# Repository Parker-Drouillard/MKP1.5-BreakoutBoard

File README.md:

# MKP1.5-BreakoutBoard
A breakout board for supporting dual extrusion &amp; 6 pwm fan control for the Rambo 1.4 

This board supports a Teensy 2.0 slave device to the Rambo 1.4 over Serial. The purpose of this board is to expand the available IO of the Rambo 1.4 to be capable of supporting a dual extrusion system, as well as additional PWM fan controls.

## About this board
This board offers 6 5v fan headers for PWM switching via a darlington array. At this current time, it does not seem the max PWM speed of the Teensy 2.0 is sufficient to run the fans at less than 100% power, so for the time being it is simply a toggle of Off or On.
The board includes a 24V to 5V buck converter, capable of supporting 3A of power, of which only 2A is anticipated to be used. Additionally, 2 ports for PT1000 passthrough, and 2 ports for E3D PT100 Amplifier boards are provided. 
An onboard L298N allows for low voltage switching of 2 independant 24V systems, one of which is being used for the second extruder solenoid, and one will be used in the future fora dynamic extruder pressure motor. Both systems have 2 encontrol pins, 1 for forward, and 1 for reverse.

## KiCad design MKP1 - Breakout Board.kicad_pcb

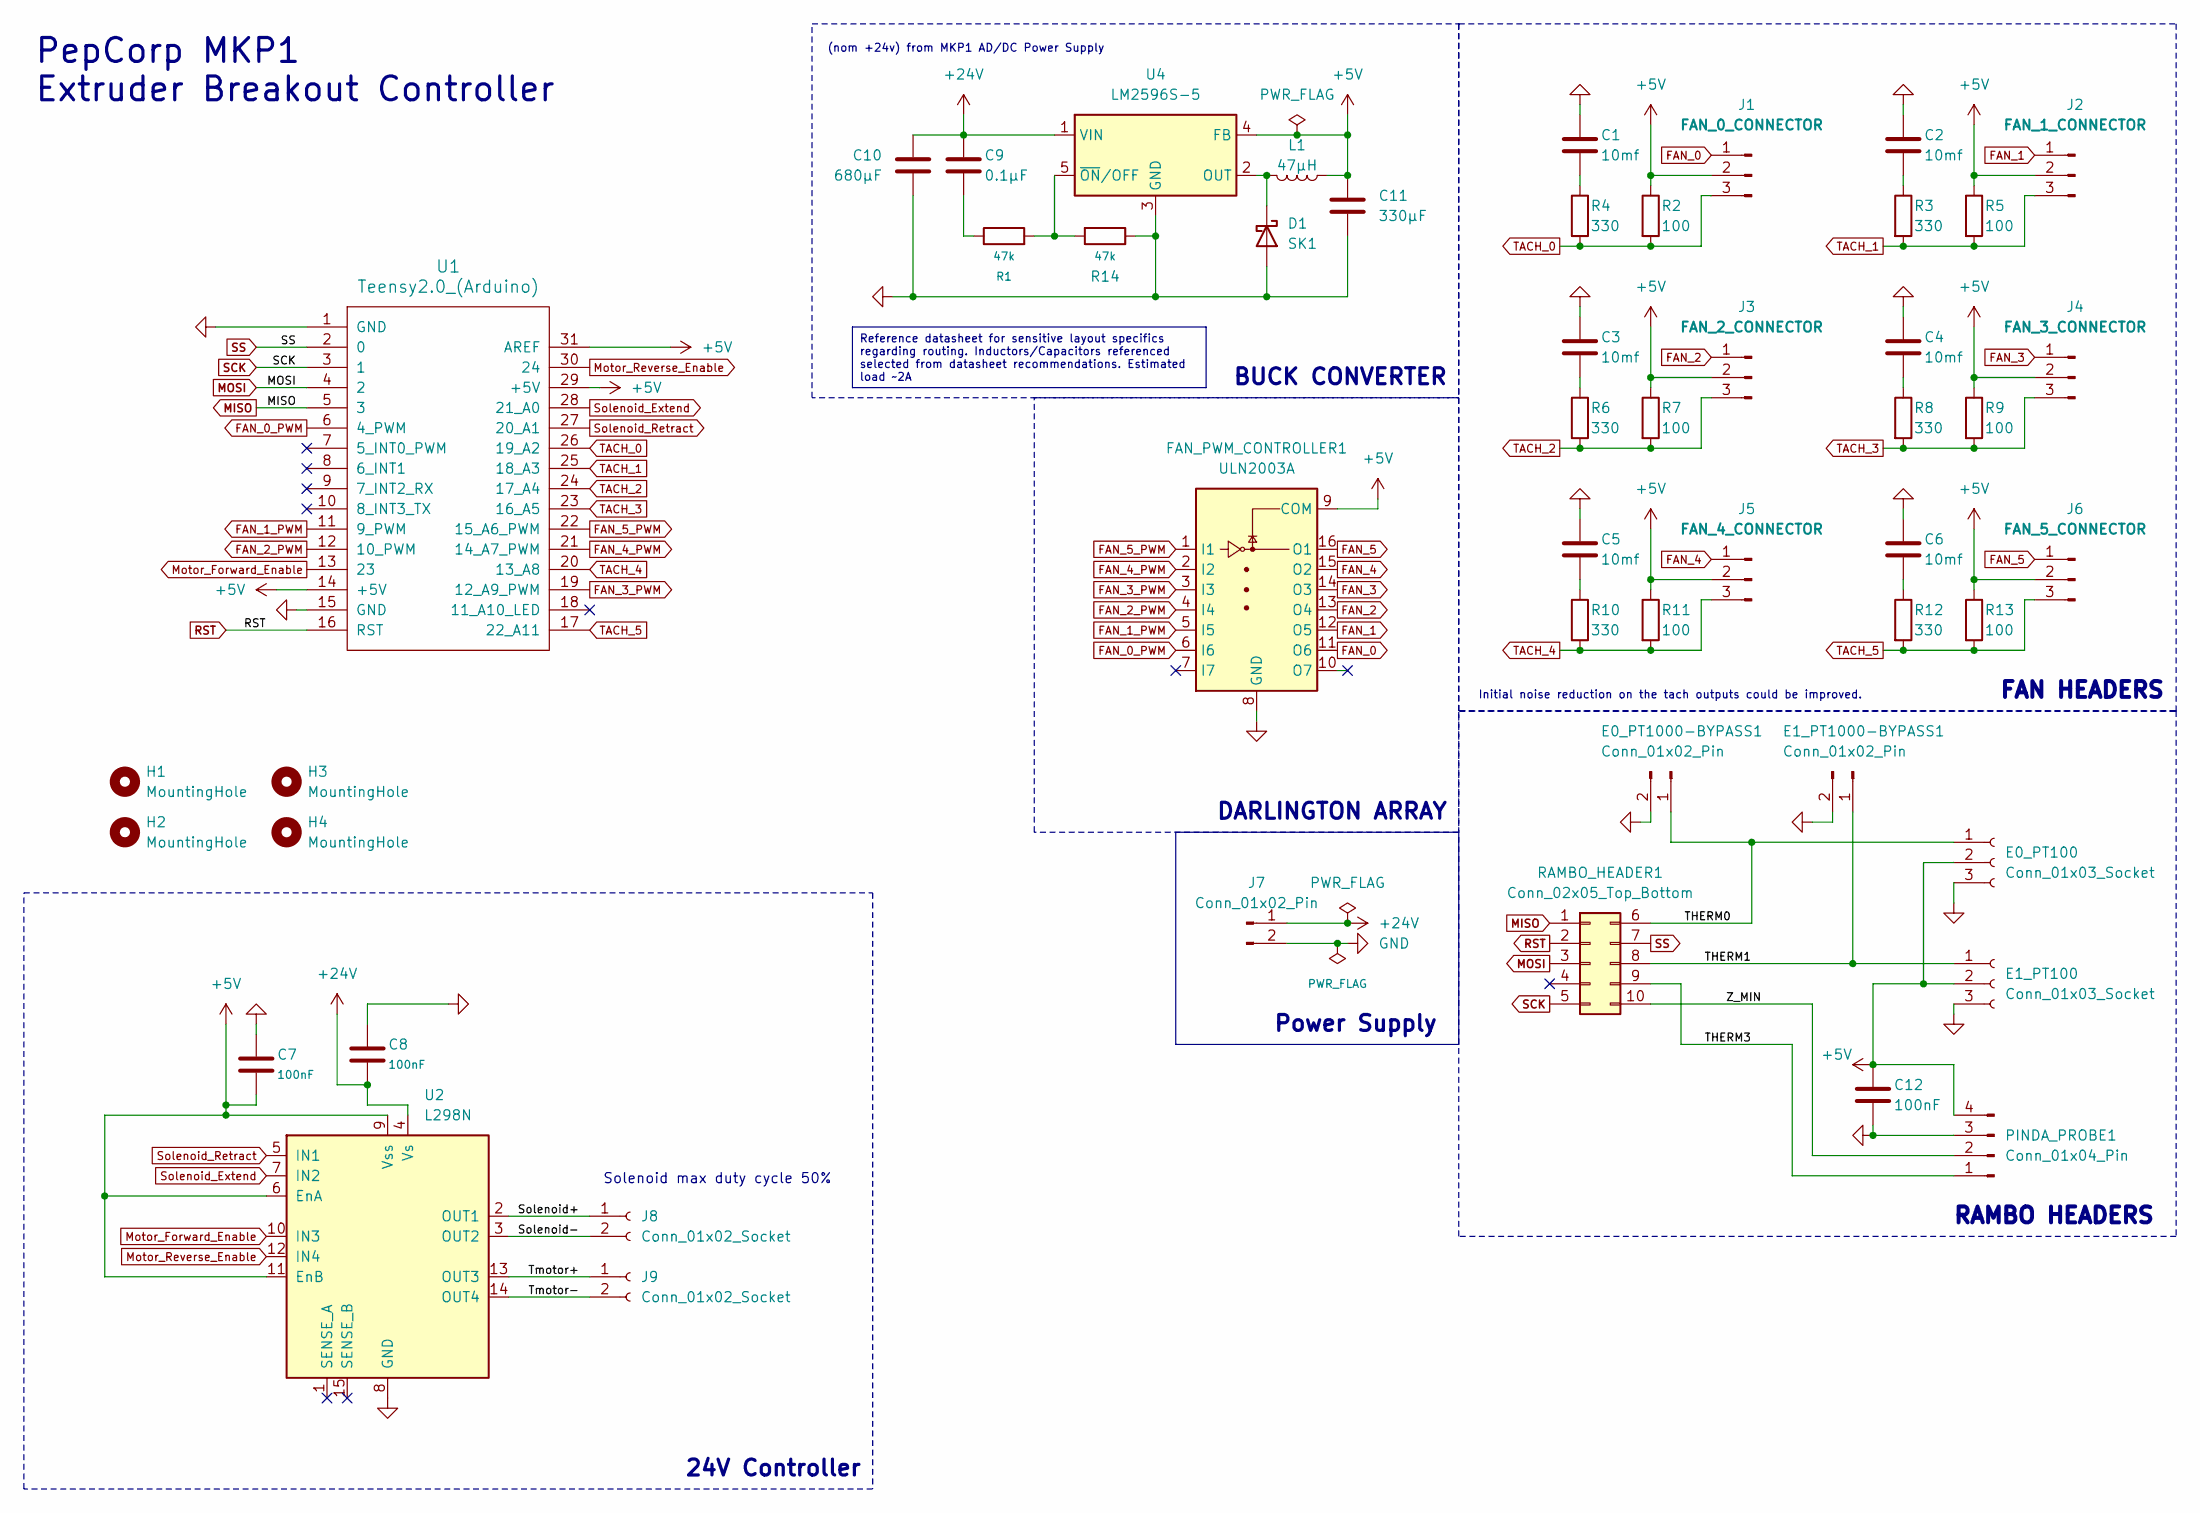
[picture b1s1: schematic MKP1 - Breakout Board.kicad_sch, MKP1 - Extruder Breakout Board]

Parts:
C1, C2, C3, C4, C5, C6: 10mf; C_0603_1608Metric_Pad1.08x0.95mm_HandSolder
C7, C8, C12: 100nF; C_0402_1005Metric_Pad0.74x0.62mm_HandSolder
C9: 0.1µF; C_0402_1005Metric_Pad0.74x0.62mm_HandSolder
C10: 680µF; C_0603_1608Metric_Pad1.08x0.95mm_HandSolder
C11: 330µF; C_0603_1608Metric_Pad1.08x0.95mm_HandSolder
D1: SK1; D_0603_1608Metric_Pad1.05x0.95mm_HandSolder
E0_PT100, E1_PT100: Conn_01x03_Socket; PinSocket_1x03_P2.00mm_Vertical
E0_PT1000-BYPASS1, E1_PT1000-BYPASS1: Conn_01x02_Pin; Molex_KK-254_AE-6410-02A_1x02_P2.54mm_Vertical
FAN_PWM_CONTROLLER1: ULN2003A; DIP-16_W7.62mm_Socket
H1, H2, H3, H4: MountingHole; MountingHole_3.2mm_M3
J1: FAN_0_CONNECTOR; Molex_KK-396_5273-03A_1x03_P3.96mm_Vertical
J2: FAN_1_CONNECTOR; Molex_KK-396_5273-03A_1x03_P3.96mm_Vertical
J3: FAN_2_CONNECTOR; Molex_KK-396_5273-03A_1x03_P3.96mm_Vertical
J4: FAN_3_CONNECTOR; Molex_KK-396_5273-03A_1x03_P3.96mm_Vertical
J5: FAN_4_CONNECTOR; Molex_KK-396_5273-03A_1x03_P3.96mm_Vertical
J6: FAN_5_CONNECTOR; Molex_KK-396_5273-03A_1x03_P3.96mm_Vertical
J7: Conn_01x02_Pin; Molex_KK-396_A-41791-0002_1x02_P3.96mm_Vertical
J8, J9: Conn_01x02_Socket; Molex_KK-254_AE-6410-02A_1x02_P2.54mm_Vertical
L1: 47µH; L_0402_1005Metric
PINDA_PROBE1: Conn_01x04_Pin; Molex_KK-396_5273-04A_1x04_P3.96mm_Vertical
R1, R14: 47k; R_0402_1005Metric
R2, R5, R7, R9, R11, R13: 100; R_0402_1005Metric
R3, R4, R6, R8, R10, R12: 330; R_0402_1005Metric
RAMBO_HEADER1: Conn_02x05_Top_Bottom; PinHeader_2x05_P2.00mm_Vertical
U1: Teensy2.0_(Arduino); Teensy2.0
U2: L298N; TO-220-15_P2.54x2.54mm_StaggerOdd_Lead4.58mm_Vertical
U4: LM2596S-5; TO-263-5_TabPin3

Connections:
+5V: C7.2, C11.1, C12.1, E0_PT100.2, E1_PT100.2, FAN_PWM_CONTROLLER1.9 (COM), J1.2, J2.2, J3.2, J4.2, J5.2, J6.2, L1.2, PINDA_PROBE1.4, R2.1, R5.1, R7.1, R9.1, R11.1, R13.1, U1.14 (+5V), U1.29 (+5V), U1.31 (AREF), U2.6 (EnA), U2.9 (Vss), U2.11 (EnB), U4.4 (FB); also elsewhere on the board
+24V: C8.2, C9.1, C10.2, J7.1, U2.4 (Vs), U4.1 (VIN)
/Solenoid+: J8.1, U2.2 (OUT1)
/Solenoid-: J8.2, U2.3 (OUT2)
/THERM0: E0_PT100.1, E0_PT1000-BYPASS1.1, RAMBO_HEADER1.6; also elsewhere on the board
/THERM1: E1_PT100.1, E1_PT1000-BYPASS1.1, RAMBO_HEADER1.8; also elsewhere on the board
/THERM3: PINDA_PROBE1.1, RAMBO_HEADER1.9; also elsewhere on the board
/Tmotor+: J9.1, U2.13 (OUT3)
/Tmotor-: J9.2, U2.14 (OUT4)
/Z_MIN: PINDA_PROBE1.2, RAMBO_HEADER1.10; also elsewhere on the board
FAN_0: FAN_PWM_CONTROLLER1.11 (O6), J1.1
FAN_0_PWM: FAN_PWM_CONTROLLER1.6 (I6), U1.6 (4_PWM)
FAN_1: FAN_PWM_CONTROLLER1.12 (O5), J2.1
FAN_1_PWM: FAN_PWM_CONTROLLER1.5 (I5), U1.11 (9_PWM)
FAN_2: FAN_PWM_CONTROLLER1.13 (O4), J3.1
FAN_2_PWM: FAN_PWM_CONTROLLER1.4 (I4), U1.12 (10_PWM)
FAN_3: FAN_PWM_CONTROLLER1.14 (O3), J4.1
FAN_3_PWM: FAN_PWM_CONTROLLER1.3 (I3), U1.19 (12_A9_PWM)
FAN_4: FAN_PWM_CONTROLLER1.15 (O2), J5.1
FAN_4_PWM: FAN_PWM_CONTROLLER1.2 (I2), U1.21 (14_A7_PWM)
FAN_5: FAN_PWM_CONTROLLER1.16 (O1), J6.1
FAN_5_PWM: FAN_PWM_CONTROLLER1.1 (I1), U1.22 (15_A6_PWM)
GND: C1.1, C2.1, C3.1, C4.1, C5.1, C6.1, C7.1, C8.1, C10.1, C11.2, C12.2, D1.2 (A), E0_PT100.3, E0_PT1000-BYPASS1.2, E1_PT100.3, E1_PT1000-BYPASS1.2, FAN_PWM_CONTROLLER1.8 (GND), J7.2, PINDA_PROBE1.3, R14.1, U1.1 (GND), U1.15 (GND), U2.8 (GND), U4.3 (GND); also elsewhere on the board
MISO: RAMBO_HEADER1.1, U1.5 (3)
MOSI: RAMBO_HEADER1.3, U1.4 (2)
Motor_Forward_Enable: U1.13 (23), U2.10 (IN3)
Motor_Reverse_Enable: U1.30 (24), U2.12 (IN4)
unnamed: C1.2, R4.1
unnamed: C2.2, R3.1
unnamed: C3.2, R6.1
unnamed: C4.2, R8.1
unnamed: C5.2, R10.1
unnamed: C6.2, R12.1
unnamed: C9.2, R1.1
unnamed: D1.1 (K), L1.1, U4.2 (OUT)
unnamed: R1.2, R14.2, U4.5 (~ON/OFF)
RST: RAMBO_HEADER1.2, U1.16 (RST)
SCK: RAMBO_HEADER1.5, U1.3 (1)
SS: RAMBO_HEADER1.7, U1.2 (0)
Solenoid_Extend: U1.28 (21_A0), U2.7 (IN2)
Solenoid_Retract: U1.27 (20_A1), U2.5 (IN1)
TACH_0: J1.3, R2.2, R4.2, U1.26 (19_A2)
TACH_1: J2.3, R3.2, R5.2, U1.25 (18_A3)
TACH_2: J3.3, R6.2, R7.2, U1.24 (17_A4)
TACH_3: J4.3, R8.2, R9.2, U1.23 (16_A5)
TACH_4: J5.3, R10.2, R11.2, U1.20 (13_A8)
TACH_5: J6.3, R12.2, R13.2, U1.17 (22_A11)

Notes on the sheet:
Reference datasheet for sensitive layout specifics regarding routing. Inductors/Capacitors referenced selected from datasheet recommendations. Estimated load ~2A
FAN HEADERS
DARLINGTON ARRAY
Solenoid max duty cycle 50%
Initial noise reduction on the tach outputs could be improved.
(nom +24v) from MKP1 AD/DC Power Supply
Power Supply
PepCorp MKP1 Extruder Breakout Controller
24V Controller
BUCK CONVERTER
RAMBO HEADERS

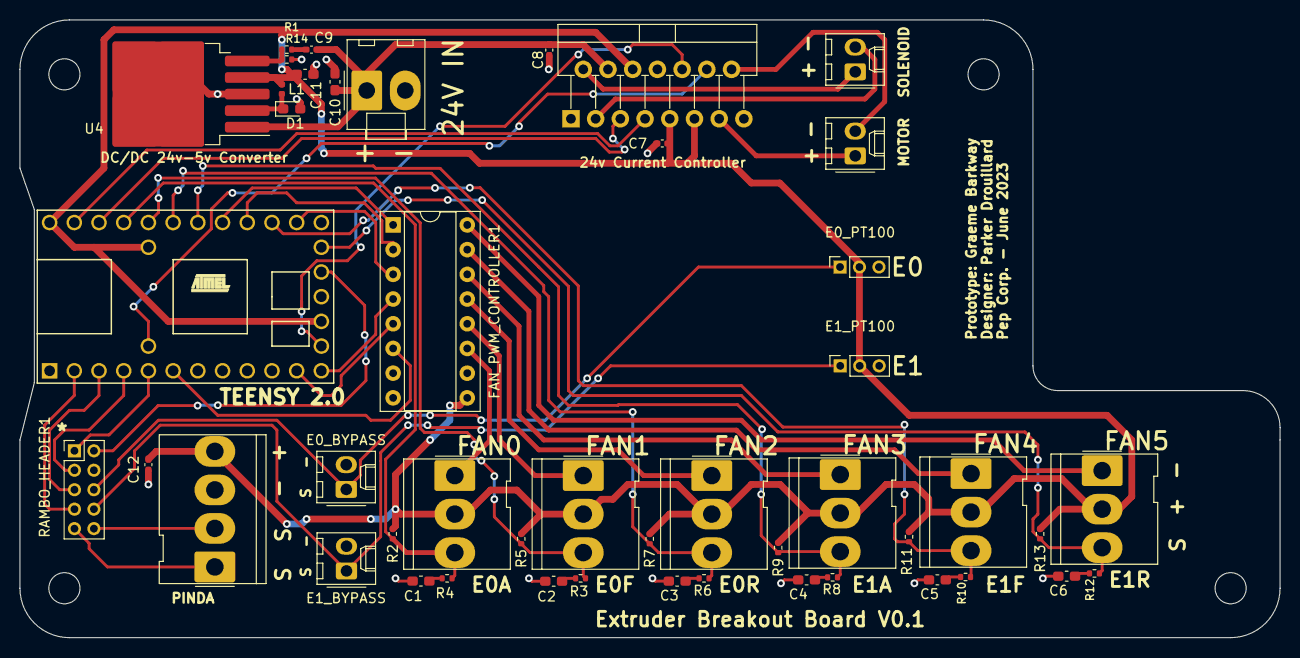
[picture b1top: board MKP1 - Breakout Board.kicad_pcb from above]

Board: 2 copper layers, 129.5 x 63.5 mm, 51 parts (0 on the bottom side), 47 nets.

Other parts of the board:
E0_BYPASS, E1_BYPASS: Conn_01x02_Pin; Molex_KK-254_AE-6410-02A_1x02_P2.54mm_Vertical
PINDA: Conn_01x04_Pin; Molex_KK-396_5273-04A_1x04_P3.96mm_Vertical

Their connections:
+5V: PINDA.4; also elsewhere on the board
/THERM0: E0_BYPASS.1; also elsewhere on the board
/THERM1: E1_BYPASS.1; also elsewhere on the board
/THERM3: PINDA.1; also elsewhere on the board
/Z_MIN: PINDA.2; also elsewhere on the board
GND: E0_BYPASS.2, E1_BYPASS.2, PINDA.3; also elsewhere on the board
